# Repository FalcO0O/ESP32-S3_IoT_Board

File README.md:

# ESP32-S3 IoT Carrier Board

A simple and versatile IO carrier board (PCB) designed to simplify the integration of IoT sensors and actuators with the ESP32S3.

## Main Features

* **5x JST 2.50mm Ports (4-pin):** Convenient connectors for easy peripheral attachment.
* **2x JST 2.50mm Ports (6-pin):** Dedicated bus connectors for I2C, SPI, or other multi-wire protocols.
* **Built-in 3.3V Regulator:** High-efficiency converter supporting up to **2A** of current.
* **Triple-Mode Pin Configuration:** Each control pin can be hardware-configured in three ways to suit your application:
    1. **Direct to ESP32:** For standard 3.3V logic and digital communication.
    2. **Voltage Divider:** Enables safe reading of higher-voltage analog or digital signals.
    3. **MOSFET Driver (Low-side switch):** For controlling high-current devices like LED strips, relays, or small motors.

## Pinout (JST 2.50mm)

All five 4-pin connectors share the same standardized pinout:

| Pin | Function | Description |
| :--- | :--- | :--- |
| **1** | `VCC (+)` | Power supply for the external device. |
| **2** | `GND (-)` | Common ground. |
| **3** | `SIG_1` | Control Pin 1 (Direct / Divider / MOSFET). |
| **4** | `SIG_2` | Control Pin 2 (Direct / Divider / MOSFET). |

## Schematics:

## Repository Contents

This repository includes all necessary files for manufacturing and assembly:
* **Schematics:** Detailed circuit diagrams.
* **Gerber Files:** Production-ready files for PCB fabrication.
* **BOM (Bill of Materials):** A complete list of required components.
* **3D Model:** The board layout in `.step` format for enclosure design.

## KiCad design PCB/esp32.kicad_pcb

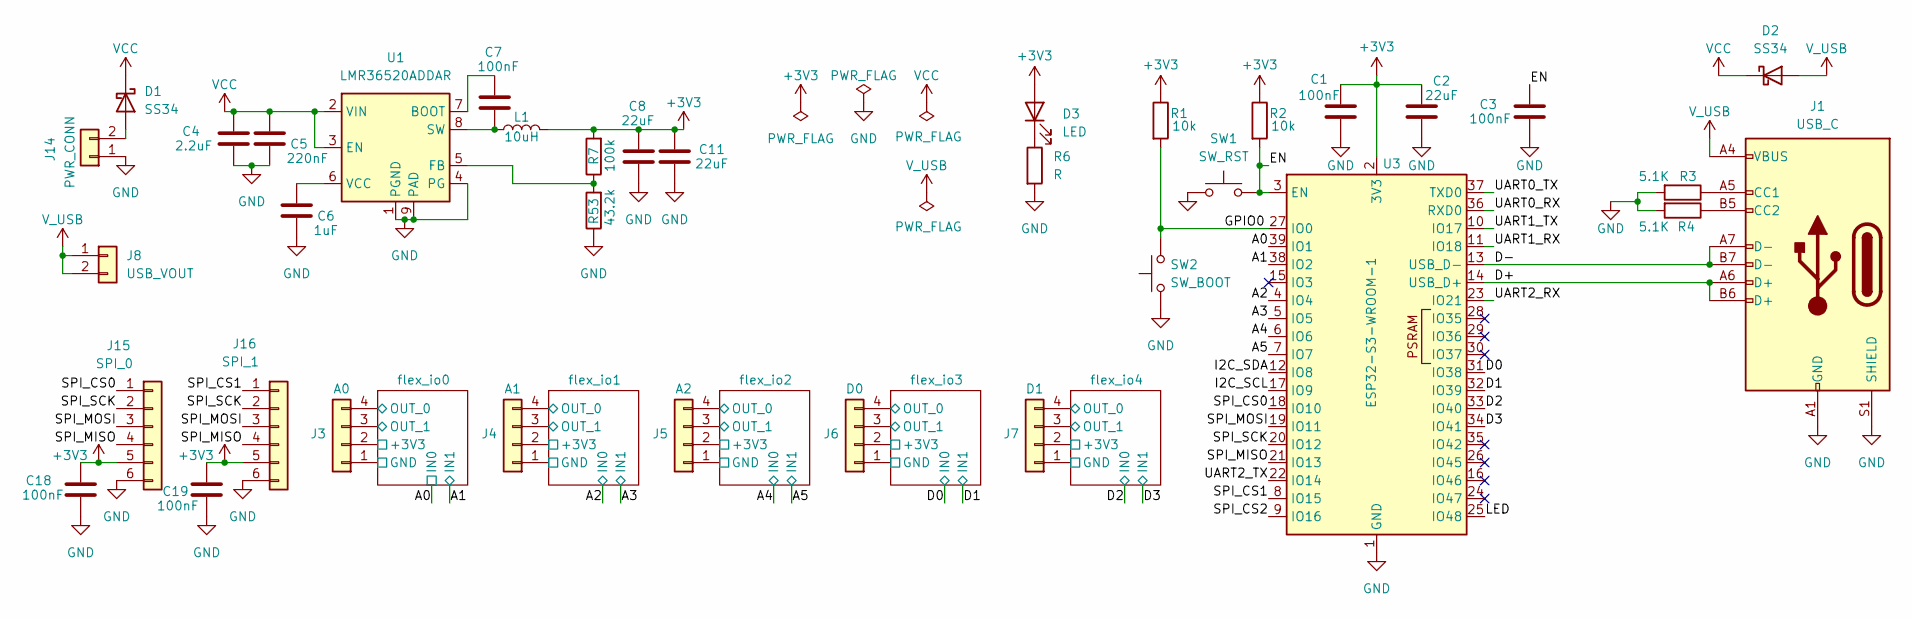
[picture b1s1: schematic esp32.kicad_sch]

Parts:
C1, C3, C7, C18, C19: 100nF; C_0805_2012Metric_Pad1.18x1.45mm_HandSolder
C2, C8, C11: 22uF; C_0805_2012Metric_Pad1.18x1.45mm_HandSolder
C4: 2.2uF; C_1206&0805
C5: 220nF; C_1206&0805
C6: 1uF; C_0805_2012Metric_Pad1.18x1.45mm_HandSolder
D1, D2: SS34; D_SMB_Handsoldering
D3: LED; LED_0805_2012Metric_Pad1.15x1.40mm_HandSolder
J1: USB_C; USB_C_Receptacle_HRO_TYPE-C-31-M-12
J3: A0; JST_XH_B4B-XH-A_1x04_P2.50mm_Vertical
J4: A1; JST_XH_B4B-XH-A_1x04_P2.50mm_Vertical
J5: A2; JST_XH_B4B-XH-A_1x04_P2.50mm_Vertical
J6: D0; JST_XH_B4B-XH-A_1x04_P2.50mm_Vertical
J7: D1; JST_XH_B4B-XH-A_1x04_P2.50mm_Vertical
J8: USB_VOUT; JST_XH_B2B-XH-A_1x02_P2.50mm_Vertical
J14: PWR_CONN; TerminalBlock_MaiXu_MX126-5.0-02P_1x02_P5.00mm
J15: SPI_0; JST_PH_B6B-PH-K_1x06_P2.00mm_Vertical
J16: SPI_1; JST_PH_B6B-PH-K_1x06_P2.00mm_Vertical
L1: 10uH; L_Chilisin_BMRA00050530
R1, R2: 10k; R_0805_2012Metric_Pad1.20x1.40mm_HandSolder
R3, R4: 5.1K; R_0805_2012Metric_Pad1.20x1.40mm_HandSolder
R6: R; R_0805_2012Metric_Pad1.20x1.40mm_HandSolder
R7: 100k; R_0805_2012Metric_Pad1.20x1.40mm_HandSolder
R53: 43.2k; R_0805_2012Metric_Pad1.20x1.40mm_HandSolder
SW1: SW_RST; SW_SPST_PTS645Sx43SMTR92
SW2: SW_BOOT; SW_SPST_PTS645Sx43SMTR92
U1: LMR36520ADDAR; Texas_HTSOP-8-1EP_3.9x4.9mm_P1.27mm_EP2.95x4.9mm_Mask2.4x3.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
U3: ESP32-S3-WROOM-1

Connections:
+3V3: C1.2, C2.2, C8.1, C11.1, C18.1, C19.1, D3.2 (A), J3.2, J4.2, J5.2, J6.2, J7.2, J15.5, J16.5, L1.2, R1.1, R2.1, R7.2, U3.2 (3V3); also elsewhere on the board
/A0: U3.39 (IO1); also elsewhere on the board
/A1: U3.38 (IO2); also elsewhere on the board
/A2: U3.4 (IO4); also elsewhere on the board
/A3: U3.5 (IO5); also elsewhere on the board
/A4: U3.6 (IO6); also elsewhere on the board
/A5: U3.7 (IO7); also elsewhere on the board
/D0: U3.31 (IO38); also elsewhere on the board
/D1: U3.32 (IO39); also elsewhere on the board
/D2: U3.33 (IO40); also elsewhere on the board
/D3: U3.34 (IO41); also elsewhere on the board
/D+: J1.A6 (D+), J1.B6 (D+), U3.14 (USB_D+)
/D-: J1.A7 (D-), J1.B7 (D-), U3.13 (USB_D-)
/EN: C3.2, R2.2, SW1.2, U3.3 (EN)
/GPIO0: R1.2, SW2.2, U3.27 (IO0)
/I2C_SCL: U3.17 (IO9)
/I2C_SDA: U3.12 (IO8)
/LED: U3.25 (IO48)
/SPI_CS0: J15.1, U3.18 (IO10)
/SPI_CS1: J16.1, U3.8 (IO15)
/SPI_CS2: U3.9 (IO16)
/SPI_MISO: J15.4, J16.4, U3.21 (IO13)
/SPI_MOSI: J15.3, J16.3, U3.19 (IO11)
/SPI_SCK: J15.2, J16.2, U3.20 (IO12)
/UART0_RX: U3.36 (RXD0)
/UART0_TX: U3.37 (TXD0)
/UART1_RX: U3.11 (IO18)
/UART1_TX: U3.10 (IO17)
/UART2_RX: U3.23 (IO21)
/UART2_TX: U3.22 (IO14)
/flex_io0/OUT_0: J3.4; also elsewhere on the board
/flex_io0/OUT_1: J3.3; also elsewhere on the board
/flex_io1/OUT_0: J4.4; also elsewhere on the board
/flex_io1/OUT_1: J4.3; also elsewhere on the board
/flex_io2/OUT_0: J5.4; also elsewhere on the board
/flex_io2/OUT_1: J5.3; also elsewhere on the board
/flex_io3/OUT_0: J6.4; also elsewhere on the board
/flex_io3/OUT_1: J6.3; also elsewhere on the board
/flex_io4/OUT_0: J7.4; also elsewhere on the board
/flex_io4/OUT_1: J7.3; also elsewhere on the board
GND: C1.1, C2.1, C3.1, C4.2, C5.2, C6.2, C8.2, C11.2, C18.2, C19.2, J1.A1 (GND), J1.A12 (GND), J1.B1 (GND), J1.B12 (GND), J1.S1 (SHIELD), J3.1, J4.1, J5.1, J6.1, J7.1, J14.1, J15.6, J16.6, R3.2, R4.2, R6.2, R53.1, SW1.1, SW2.1, U1.1 (PGND), U1.4 (PG), U1.9 (PAD), U3.1 (GND), U3.40 (GND), U3.41 (GND); also elsewhere on the board
unnamed: D1.2 (A), J14.2
unnamed: D3.1 (K), R6.1
unnamed: J1.A5 (CC1), R3.1
unnamed: J1.B5 (CC2), R4.1
unnamed: C7.1, U1.7 (BOOT)
unnamed: R7.1, R53.2, U1.5 (FB)
unnamed: C7.2, L1.1, U1.8 (SW)
unnamed: C6.1, U1.6 (VCC)
VCC: C4.1, C5.1, D1.1 (K), D2.1 (K), U1.2 (VIN), U1.3 (EN)
V_USB: D2.2 (A), J1.A4 (VBUS), J1.A9 (VBUS), J1.B4 (VBUS), J1.B9 (VBUS), J8.1, J8.2

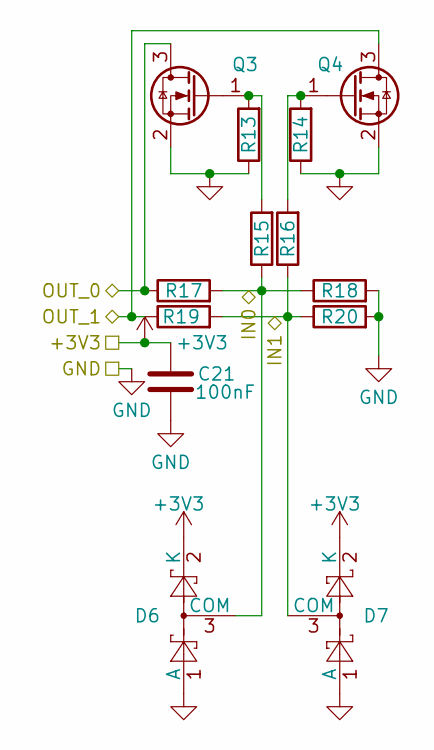
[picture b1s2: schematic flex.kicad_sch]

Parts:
C21: 100nF; C_0805_2012Metric_Pad1.18x1.45mm_HandSolder
D6, D7: BAT54S; SOT-23
Q3, Q4: AO3400A; SOT-23
R13, R14: 220R; R_0805_2012Metric_Pad1.20x1.40mm_HandSolder
R15, R16, R17, R18, R19, R20: 0; R_0805_2012Metric_Pad1.20x1.40mm_HandSolder

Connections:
+3V3: C21.1, D6.2 (K), D7.2 (K); also elsewhere on the board
/A2: D6.3 (COM), R15.1, R17.2, R18.1; also elsewhere on the board
/A3: D7.3 (COM), R16.1, R19.2, R20.1; also elsewhere on the board
/flex_io1/OUT_0: Q3.3 (D), R17.1; also elsewhere on the board
/flex_io1/OUT_1: Q4.3 (D), R19.1; also elsewhere on the board
GND: C21.2, D6.1 (A), D7.1 (A), Q3.2 (S), Q4.2 (S), R13.1, R14.1, R18.2, R20.2; also elsewhere on the board
unnamed: Q3.1 (G), R13.2, R15.2
unnamed: Q4.1 (G), R14.2, R16.2

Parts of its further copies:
C22, C23, C24, C25: 100nF; C_0805_2012Metric_Pad1.18x1.45mm_HandSolder
D8, D9, D10, D11, D12, D13, D14, D15: BAT54S; SOT-23
Q5, Q6, Q7, Q8, Q9, Q10, Q11, Q12: AO3400A; SOT-23
R21, R22, R29, R30, R37, R38, R45, R46: 220R; R_0805_2012Metric_Pad1.20x1.40mm_HandSolder
R23, R24, R25, R26, R27, R28, R31, R32, R33, R34, R35, R36, R39, R40, R41, R42, R43, R44, R47, R48, R49, R50, R51, R52: 0; R_0805_2012Metric_Pad1.20x1.40mm_HandSolder

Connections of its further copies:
+3V3: C22.1, C23.1, C24.1, C25.1, D8.2 (K), D9.2 (K), D10.2 (K), D11.2 (K), D12.2 (K), D13.2 (K), D14.2 (K), D15.2 (K); also elsewhere on the board
/A0: D10.3 (COM), R31.1, R33.2, R34.1; also elsewhere on the board
/A1: D11.3 (COM), R32.1, R35.2, R36.1; also elsewhere on the board
/A4: D8.3 (COM), R23.1, R25.2, R26.1; also elsewhere on the board
/A5: D9.3 (COM), R24.1, R27.2, R28.1; also elsewhere on the board
/D0: D12.3 (COM), R39.1, R41.2, R42.1; also elsewhere on the board
/D1: D13.3 (COM), R40.1, R43.2, R44.1; also elsewhere on the board
/D2: D14.3 (COM), R47.1, R49.2, R50.1; also elsewhere on the board
/D3: D15.3 (COM), R48.1, R51.2, R52.1; also elsewhere on the board
/flex_io0/OUT_0: Q7.3 (D), R33.1; also elsewhere on the board
/flex_io0/OUT_1: Q8.3 (D), R35.1; also elsewhere on the board
/flex_io2/OUT_0: Q5.3 (D), R25.1; also elsewhere on the board
/flex_io2/OUT_1: Q6.3 (D), R27.1; also elsewhere on the board
/flex_io3/OUT_0: Q9.3 (D), R41.1; also elsewhere on the board
/flex_io3/OUT_1: Q10.3 (D), R43.1; also elsewhere on the board
/flex_io4/OUT_0: Q11.3 (D), R49.1; also elsewhere on the board
/flex_io4/OUT_1: Q12.3 (D), R51.1; also elsewhere on the board
GND: C22.2, C23.2, C24.2, C25.2, D8.1 (A), D9.1 (A), D10.1 (A), D11.1 (A), D12.1 (A), D13.1 (A), D14.1 (A), D15.1 (A), Q5.2 (S), Q6.2 (S), Q7.2 (S), Q8.2 (S), Q9.2 (S), Q10.2 (S), Q11.2 (S), Q12.2 (S), R21.1, R22.1, R26.2, R28.2, R29.1, R30.1, R34.2, R36.2, R37.1, R38.1, R42.2, R44.2, R45.1, R46.1, R50.2, R52.2; also elsewhere on the board
unnamed: Q5.1 (G), R21.2, R23.2
unnamed: Q6.1 (G), R22.2, R24.2
unnamed: Q7.1 (G), R29.2, R31.2
unnamed: Q8.1 (G), R30.2, R32.2
unnamed: Q9.1 (G), R37.2, R39.2
unnamed: Q10.1 (G), R38.2, R40.2
unnamed: Q11.1 (G), R45.2, R47.2
unnamed: Q12.1 (G), R46.2, R48.2

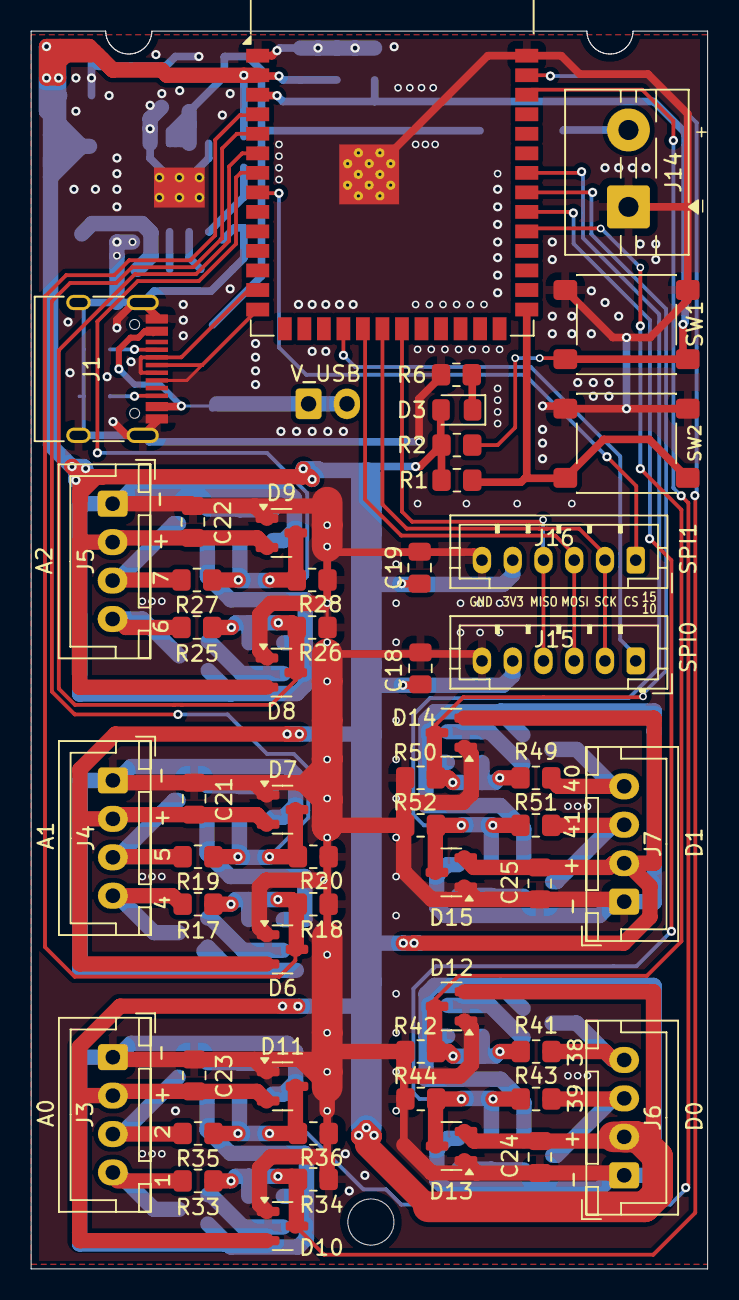
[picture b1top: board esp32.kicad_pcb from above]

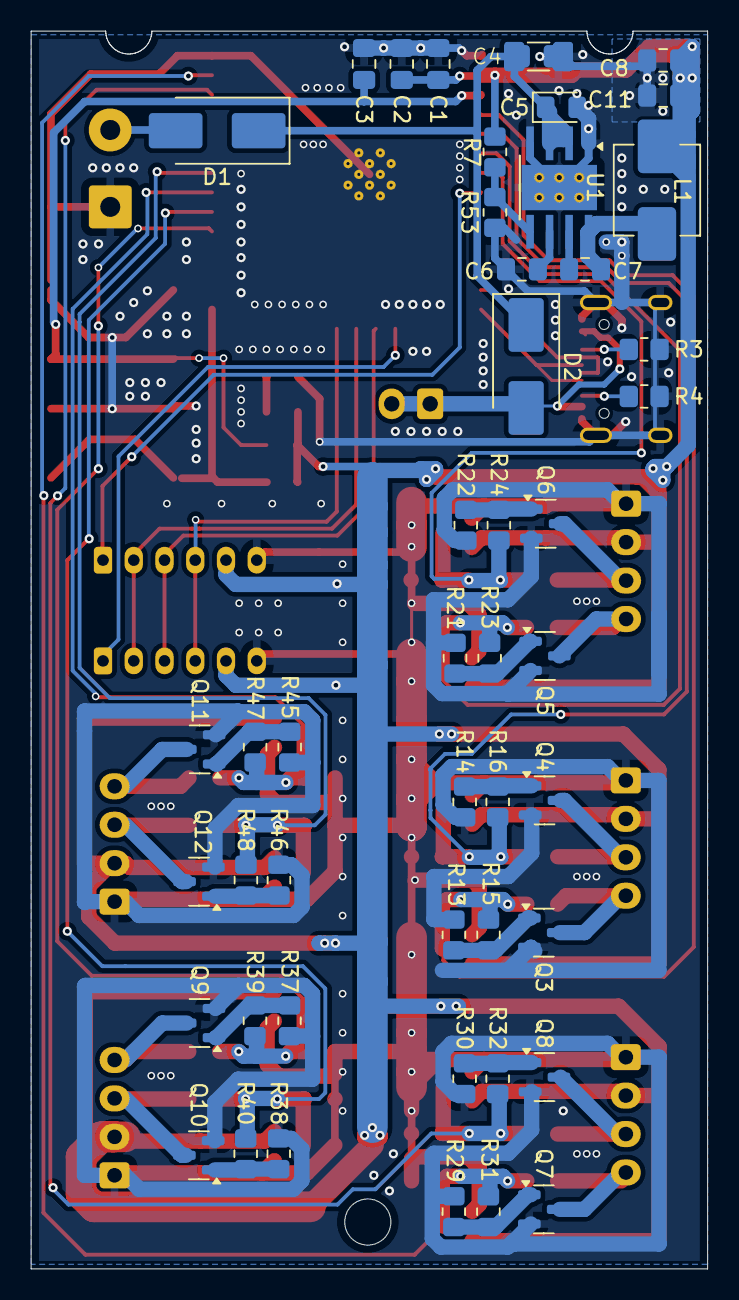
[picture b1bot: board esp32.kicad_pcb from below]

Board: 2 copper layers, 44.0 x 80.5 mm, 101 parts (47 on the bottom side), 51 nets.

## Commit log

2026-02-26 transopts
2026-02-26 change to mosfets and votage divider
2026-02-28 ldo version
2026-03-02 LMR36520 version
2026-03-02 rest components placed
2026-03-02 with CH340
2026-03-02 without uart converter, small version
2026-03-03 change footprints for better soldering
2026-03-03 remove vias from pads
2026-03-03 swap diode place
2026-03-03 change footprint of Vusb
2026-03-04 move inductor
2026-03-04 fix power supply module layout
2026-03-04 add ground plane
2026-03-29 review passed
2026-03-29 add silkscreen
2026-03-29 move bottom to align center
2026-03-29 done
2026-03-29 add gerbers
2026-03-29 final touch
2026-03-29 add docs
2026-03-29 refactor
2026-03-29 Add README
    Added detailed information about the IO Expansion Board for ESP32S3, including features, pinout, and repository contents.
2026-03-29 Revise README title and description for clarity
    Updated the title and description to reflect the correct terminology for the board.
2026-05-28 fix usb differential pair
